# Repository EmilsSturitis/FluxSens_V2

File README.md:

# FluxSens_V2
PCB with drv5053, OPA2333 and Raspberry pi Pico, for a single board flux sens development

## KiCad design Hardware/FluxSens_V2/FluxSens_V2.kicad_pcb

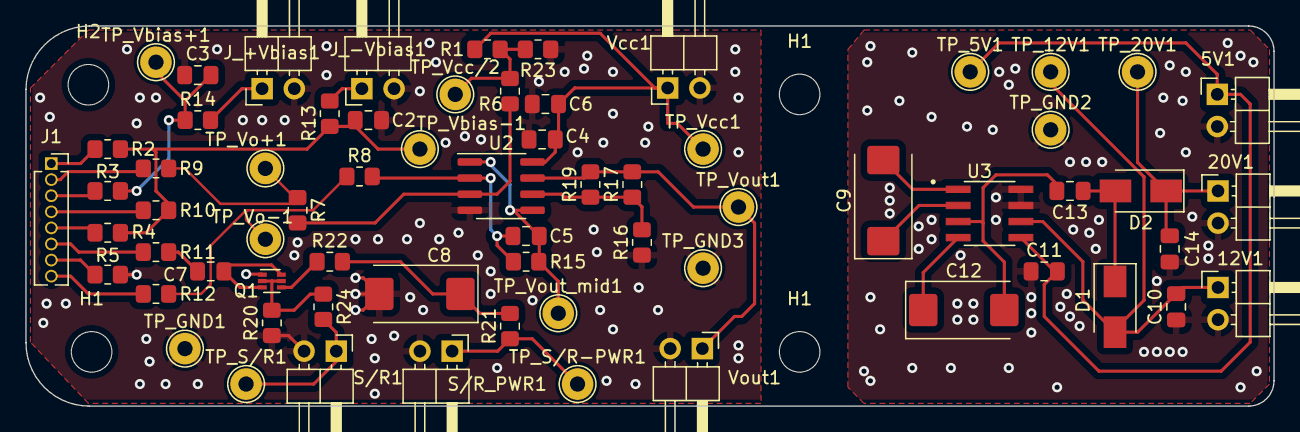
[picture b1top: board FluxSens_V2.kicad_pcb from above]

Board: 2 copper layers, 98.5 x 30.0 mm, 71 parts (0 on the bottom side), 38 nets.

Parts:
5V1, 12V1, 20V1: Conn_01x02; PinHeader_1x02_P2.54mm_Horizontal
C2, C3, C4: 1uF; C_0805_2012Metric_Pad1.18x1.45mm_HandSolder
C5, C10, C13, C14: 100nF; C_0805_2012Metric_Pad1.18x1.45mm_HandSolder
C6, C7: 0.1uF; C_0805_2012Metric_Pad1.18x1.45mm_HandSolder
C8, C9, C12: C_Polarized_Small; CP_EIA-7343-31_Kemet-D_Pad2.25x2.55mm_HandSolder
C11: 2uf; C_0805_2012Metric_Pad1.18x1.45mm_HandSolder
D1, D2: 1N5818; D_SMA
H1, H1#2, H1#3, H2: MountingHole; MountingHole_3.2mm_M3
J1: Conn_01x08; PinSocket_1x08_P1.27mm_Vertical
J_+Vbias1: Conn_01x02; PinHeader_1x02_P2.54mm_Horizontal
J_-Vbias1: Conn_01x02; PinHeader_1x02_P2.54mm_Horizontal
Q1: BSD235C; SOT-563
R1, R23: 10k; R_0805_2012Metric_Pad1.20x1.40mm_HandSolder
R2, R3, R4, R5, R9, R10, R11, R12, R22, R24: 0R; R_0805_2012Metric_Pad1.20x1.40mm_HandSolder
R6, R15: 500k; R_0805_2012Metric_Pad1.20x1.40mm_HandSolder
R7, R8: 5k; R_0805_2012Metric_Pad1.20x1.40mm_HandSolder
R13, R14: 4R; R_0805_2012Metric_Pad1.20x1.40mm_HandSolder
R16: Rb; R_0805_2012Metric_Pad1.20x1.40mm_HandSolder
R17: Ra; R_0805_2012Metric_Pad1.20x1.40mm_HandSolder
R19: Rth; R_0805_2012Metric_Pad1.20x1.40mm_HandSolder
R20: 4k7; R_0805_2012Metric_Pad1.20x1.40mm_HandSolder
R21: 180R; R_0805_2012Metric_Pad1.20x1.40mm_HandSolder
S/R1: Conn_01x02; PinHeader_1x02_P2.54mm_Horizontal
S/R_PWR1: Conn_01x02; PinHeader_1x02_P2.54mm_Horizontal
TP_5V1, TP_12V1, TP_20V1: TestPoint; TestPoint_THTPad_D2.5mm_Drill1.2mm
TP_GND1, TP_GND2, TP_GND3: TestPoint; TestPoint_THTPad_D2.5mm_Drill1.2mm
TP_S/R1: TestPoint; TestPoint_THTPad_D2.5mm_Drill1.2mm
TP_S/R-PWR1: TestPoint; TestPoint_THTPad_D2.5mm_Drill1.2mm
TP_Vbias+1: TestPoint; TestPoint_THTPad_D2.5mm_Drill1.2mm
TP_Vbias-1: TestPoint; TestPoint_THTPad_D2.5mm_Drill1.2mm
TP_Vcc1: TestPoint; TestPoint_THTPad_D2.5mm_Drill1.2mm
TP_Vcc/2: TestPoint; TestPoint_THTPad_D2.5mm_Drill1.2mm
TP_Vo+1: TestPoint; TestPoint_THTPad_D2.5mm_Drill1.2mm
TP_Vo-1: TestPoint; TestPoint_THTPad_D2.5mm_Drill1.2mm
TP_Vout1: TestPoint; TestPoint_THTPad_D2.5mm_Drill1.2mm
TP_Vout_mid1: TestPoint; TestPoint_THTPad_D2.5mm_Drill1.2mm
U2: RC4558; SOIC-8_3.9x4.9mm_P1.27mm
U3: MAX662ACSA+; SOIC127P600X175-8N
Vcc1: Conn_01x02; PinHeader_1x02_P2.54mm_Horizontal
Vout1: Conn_01x02; PinHeader_1x02_P2.54mm_Horizontal

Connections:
/5V: 5V1.1, C11.2, TP_5V1.1, U3.5 (VCC)
/20V: 20V1.1, C14.2, D2.1 (K), TP_20V1.1
/+12V: 12V1.1, C10.2, D1.2 (A), TP_12V1.1, U3.6 (VOUT)
/+Vbias: C3.2, R3.2, R14.1, TP_Vbias+1.1
/-Vbias: C2.2, R2.2, R4.2, R10.2, R13.1, TP_Vbias-1.1
/S/R: Q1.2 (GN), Q1.5 (GP), R20.2, R24.1
/S/R+: C7.1, R11.2
/Vcc: C4.2, C6.2, R1.2, TP_Vcc1.1, U2.8 (V+), Vcc1.1
/Vcc/2: R1.1, R6.1, R23.2, TP_Vcc/2.1
/Vo: R17.2, R19.2, TP_Vout1.1, U2.7, Vout1.1
/Vo+: R7.1, R9.2, TP_Vo+1.1
/Vo-: R8.1, R12.2, TP_Vo-1.1
GND: C2.1, C3.1, C4.1, C6.1, C8.2, J_+Vbias1.2, J_-Vbias1.2, Q1.1 (SN), R5.2, R16.1, R20.1, R23.1, S/R1.2, S/R_PWR1.2, TP_GND1.1, TP_GND3.1, U2.4 (V-), Vcc1.2, Vout1.2
GND2: 5V1.2, 12V1.2, 20V1.2, C10.1, C11.1, C14.1, TP_GND2.1, U3.7 (GND), U3.8 (SHDN)
unnamed: C5.1, R8.2, R15.1, U2.2 (-)
unnamed: C5.2, R15.2, TP_Vout_mid1.1, U2.1, U2.5 (+)
unnamed: C7.2, Q1.3 (DP), Q1.6 (DN)
unnamed: C8.1, R21.2, R22.2
unnamed: C9.1, U3.2 (C1+)
unnamed: C9.2, U3.1 (C1-)
unnamed: C12.1, U3.4 (C2+)
unnamed: C12.2, C13.2, U3.3 (C2-)
unnamed: C13.1, D1.1 (K), D2.2 (A)
unnamed: J1.1, R2.1
unnamed: J1.2, R9.1
unnamed: J1.3, R3.1
unnamed: J1.4, R10.1
unnamed: J1.5, R4.1
unnamed: J1.6, R11.1
unnamed: J1.7, R5.1
unnamed: J1.8, R12.1
unnamed: J_+Vbias1.1, R14.2
unnamed: J_-Vbias1.1, R13.2
unnamed: Q1.4 (SP), R22.1
unnamed: R6.2, R7.2, U2.3 (+)
unnamed: R16.2, R17.1, R19.1, U2.6 (-)
unnamed: R21.1, S/R_PWR1.1, TP_S/R-PWR1.1
unnamed: R24.2, S/R1.1, TP_S/R1.1

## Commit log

2022-10-03 Sensor changed to HMC1051z
2022-11-18 finished the V2 board layout
